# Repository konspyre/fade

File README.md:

## fade - A fancier attempt at a dedicated volume control

### Work in progress

This is a generalized development board for V-USB, using the ATTiny85 without a
crystal.

The board files are free for re-use, modification, and manufacture without
restriction.

The repository here contains KiCAD sources (schematic/board files),
basic V-USB code that implements a key-based HID media controller
(with modifications for this board) and a Bill of Materials listing.

***Note***: The VID/PID need to be properly defined before using this board in
production. This should be your own VID/PID, or from a source such as
[http://pid.codes](http://pid.codes).

## Usable pins

| Pin on ATTiny | Goes to | Connected to ISP as
|---|---|---|
| PB0 | Pin 2 on connector | MOSI
| PB3 | Pin 3 on connector | Not Connected
| PB4 | Pin 4 on connector | Not Connected

## Bill of Materials

#### This builds one board

| Quantity | Placement | Description | Digikey Part Number | Notes |
|---|---|---|---|---|
|1|Center, with corner dot aligned to silkscreened dot |ATTiny85 (PDIP)|ATTINY85-20PU-ND|ATTiny in PDIP format
|1|2.2K|2.2K ohm resistor|1276-5070-1-ND|Pull-up resistor for D- (0603 imperial)
|1|4.7K|4.7k ohm resistor|P4.7KGCT-ND|Pull-up resistor for AVR RESET line (0603 imperial)
|1|C1|10uF 16V 20% X6S capacitor|490-10499-1-ND|Bypass at USB input (0805 imperial)
|1|C2|0.1uF capacitor|490-1532-1-ND|Just buy a bunch. Singles are expensive! (0603 imperial)
|1|USB box at board edge (4 pads with plated through-holes)|USB connector|WM17116CT-ND|Mini USB-B
|2|68R|68 ohm resistor|311-68GRCT-ND|USB data terminators (0603 imperial)
|2|D1+D2 with striped side opposite board markings|3.6V Zener diode|BZT52C3V6-E3-08-ND|SOD123 format

#### Optional components

| Quantity | Placement | Description | Digikey Part Number | Notes
|---|---|---|---|---|
|1|ATTiny footprint (aligned with the U silk)|8 pin DIP socket|A120347-ND|The older socket used in prototypes was P/N 390261-2 and was discontinued
|1|330R|330 ohm resistor|1276-5050-1-ND|Current limiting resistor for PWR LED
|1|Next to 330R (+ - silk)|Power LED|475-2512-1-ND|Red LED 0603 imperial
|1|+5V / GND silk-screened box|Right angle 1x5 female header|S5480-ND|For connecting to carrier boards (female header)
|1|+5V / GND silkscreened box|Right angle 1x5 male header|S1121E-05-ND|For connecting to carrier boards (male header)
|1|2x3 header|6 pin AVR ISP header|3M9459-ND|For flashing the ATTiny85

## Flashing firmware

Ensure that you have all the avr tools necessary to compile the firmware. On
Debian/Ubuntu based systems the dependencies are:

    sudo apt-get install -y build-essential gcc-avr gdb-avr binutils-avr avr-libc avrdude

In the firmware directory (depending on how your system permissions are setup pre-pending `sudo` may be necessary):

    cd firmware
    make hex
    make program
    make fuse

## Fuses (important)

These must be programmed, otherwise your board will not
enumerate with the host.

    avrdude -c buspirate -p attiny85 -P /dev/ttyUSB0
     -U hfuse:w:0xdd:m -U lfuse:w:0xe1:m

## Schematic

#### License

Board files, schematic and PCB are **CC0 1.0 Universal**.

V-USB firmware and accompanying source code is **GPL 2.0 licensed**.

For more information and full license text, see the LICENSE.md file in this
repository.

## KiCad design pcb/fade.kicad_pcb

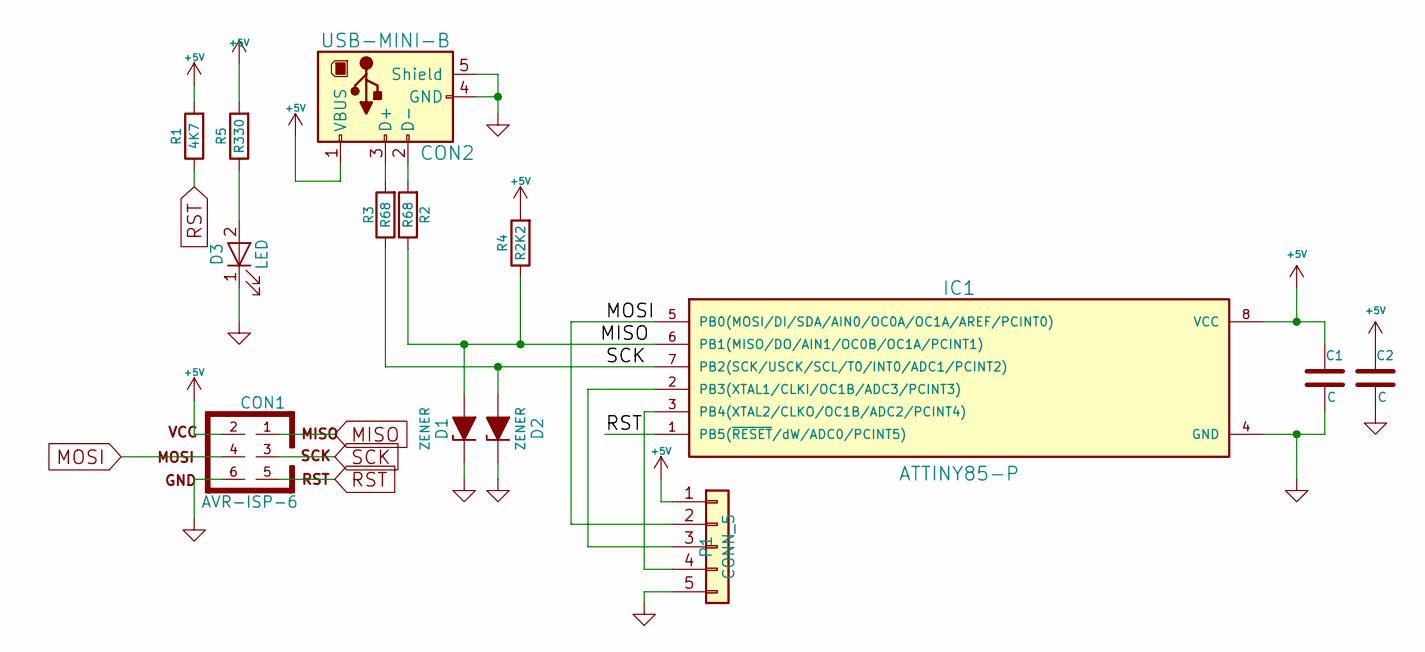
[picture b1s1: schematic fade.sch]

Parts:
C1, C2: C
CON1: AVR-ISP-6
CON2: USB-MINI-B; USB_MINI_B_SMT
D1, D2: ZENER
D3: LED
IC1: ATTINY85-P; DIP8
P1: CONN_5
R1: 4K7
R2, R3: R68
R4: R2K2
R5: R330

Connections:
+5V: C1.1, C2.1, CON1.2, CON2.1 (VBUS), IC1.8 (VCC), P1.1, R1.2, R4.2, R5.2
GND: C1.2, C2.2, CON1.6, CON2.4 (GND), CON2.5 (Shield), D1.1 (K), D2.1 (K), D3.1 (K), IC1.4 (GND), P1.5
MISO: CON1.1, D1.2 (A), IC1.6 (PB1(MISO/DO/AIN1/OC0B/OC1A/PCINT1)), R2.1, R4.1
MOSI: CON1.4, IC1.5 (PB0(MOSI/DI/SDA/AIN0/OC0A/OC1A/AREF/PCI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), P1.2
unnamed: CON2.2 (D-), R2.2
unnamed: CON2.3 (D+), R3.2
unnamed: D3.2 (A), R5.1
unnamed: IC1.2 (PB3(XTAL1/CLKI/OC1B/ADC3/PCINT3)), P1.3
unnamed: IC1.3 (PB4(XTAL2/CLKO/OC1B/ADC2/PCINT4)), P1.4
RST: CON1.5, IC1.1 (PB5(~RESET~/dW/ADC0/PCINT5)), R1.1
SCK: CON1.3, D2.2 (A), IC1.7 (PB2(SCK/USCK/SCL/T0/INT0/ADC1/PCINT2)), R3.1

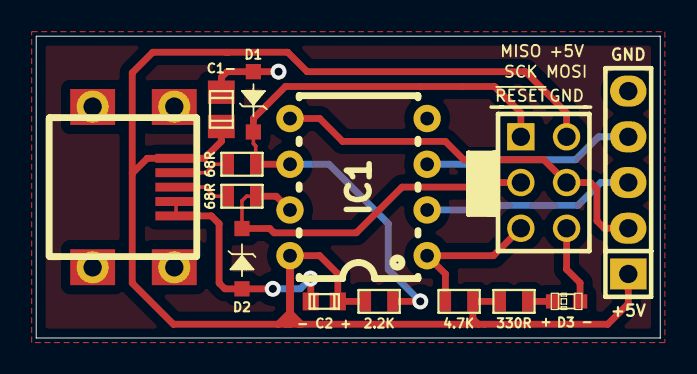
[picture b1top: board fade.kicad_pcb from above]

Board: 2 copper layers, 34.7 x 16.8 mm, 14 parts (0 on the bottom side), 11 nets.

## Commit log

2015-05-28 Add LICENSE
2015-06-01 Add schematic, pinout, BOM and license information
2015-06-01 Add PCB and parts
2015-06-01 Fix tables
2015-06-01 Add 0.1uF capacitor part used on prototypes
2015-06-01 Remove firmware README
2015-06-02 Add USB Product ID 0xFADE on Vendor ID 0x1209 (pid.codes)
    For historical reference, a USB Vendor ID currently costs US $5,000 (2015).
    USB.org accepts Visa, Mastercard, or American Express as payment.
    Thanks to pid.codes for making their donated VID block available to
    projects like these.
2015-07-06 Remove unsourced messages (components acquired)
2017-05-04 Update BOM
2017-05-04 Update silkscreen
    - Switched naming to "1209: Fade" to reflect VID/PID
    - A placement label for the optional power LED is now present
2017-05-04 Add a kicad .gitignore
2017-05-05 Add more helpful silkscreen
2018-05-08 Updated fade against KiCad 4.0.7
    Note: DRC is broken, but this board's layout has not changed (it
    should still be fabbable with a desktop PCB milling machine).
